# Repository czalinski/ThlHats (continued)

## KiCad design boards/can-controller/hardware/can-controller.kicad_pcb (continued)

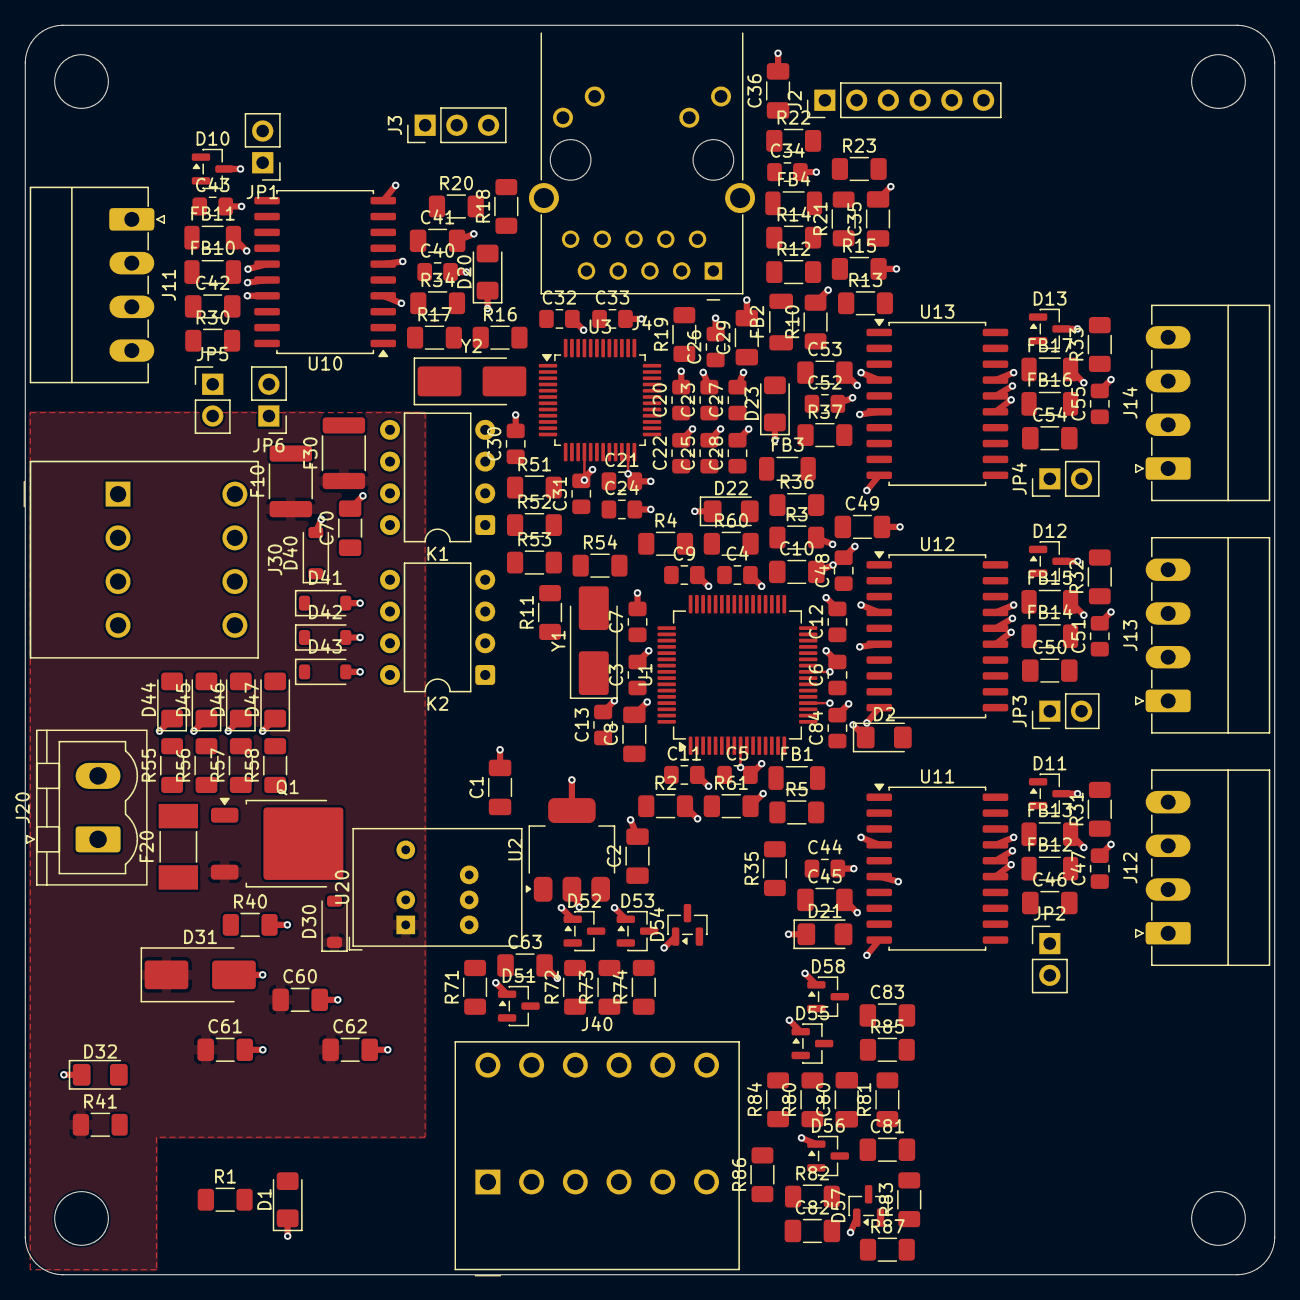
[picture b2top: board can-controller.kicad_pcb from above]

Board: 2 copper layers, 100.0 x 100.0 mm, 184 parts (0 on the bottom side), 129 nets.

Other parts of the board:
MH1, MH2, MH3, MH4: MountingHole_4.3mm_M4_Standoff7mm

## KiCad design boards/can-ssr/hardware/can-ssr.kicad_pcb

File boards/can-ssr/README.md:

# CAN SSR

Remote CAN FD node that turns a Mean Well adjustable supply into a simple
automatable DUT supply: high-side switch with reverse blocking, V and I
readback, remote voltage/current programming, auto-off when the host stops repeating its SET (failsafe timeout set by the host in each SET).
Requirements: [`docs/requirements.md`](../../docs/requirements.md), sections
4.2, 4.2.1 (builds and switching) and 4.2.2 (block diagram).

- Board: 100 x 100 mm, 2 layers, rev A (smaller welcome, not required)
- Mounting: stack interface (docs/requirements.md 4.4): 4 x M4 holes on a
  91 x 91 mm square, insulating (glass-filled nylon) 7 mm hex standoffs. Stacks
  up to 4 high on a can-controller, or screws to a DIN base plate on its own.
  No Pi holes, no DIN clips on the board (see board.json).
- Off the Pi header; powered from the 4-wire CAN cable (12 V)
- MCU: PIC18F47Q84-I/PT (TQFP-44), on the CAN/logic side

## Builds (one PCB, one firmware image)

| Build | MOSFETs (4 x D2PAK) | Max supply | Continuous |
|-------|---------------------|------------|------------|
| HC  | IPB021N10NM5LF2 | 60 V  | 50 A |
| STD | IPB107N20N3G   | 150 V | 25 A |
| HV  | IPB407N30N      | 200 V | 12 A (sequenced turn-on only) |

The only other difference is the **build resistor**, which sets the hardware
overcurrent trip threshold and is read by the PIC as the build ID.

## Functional blocks

| Block | Baseline parts | Domain |
|-------|----------------|--------|
| CAN, power, MCU | CAN FD transceiver, 12 V to 5 V buck, PIC18F47Q84-I/PT, address switch, termination jumper | CAN/logic |
| Display | MAX7219 (obsolete: replace in rev B, docs/rev-b-changes.md), 4-digit 7-segment LED, V/A indicators | CAN/logic |
| Overcurrent trip | Comparator + latch on the ACS770 output, threshold from the build resistor | CAN/logic |
| Barrier | 2 x VOM1271T, ACS770LCB-100U, ISO1640 I2C isolator, isolated DC-DC, photorelay | crosses |
| Power path | 4 x MOSFET (two per side, common source), gate network with slew C, freewheel diode, busbars, 4 bolts | load |
| Sense and programming | Vin/Vout dividers (~42 Hz RC), 2 x MCP3426 ADC (240 SPS each), 2 x MCP4725 DAC (Mean Well PV, PC), TLP240A remote on/off | load |

## Layout rules

- Busbar runs are mask-free top copper; four bolted ring-lug connections
  (supply +/-, load +/-).
- 250 V working clearances; about 6 mm creepage between the load side and the
  CAN/logic side. No copper pour joins the domains.

## Indicators and labels

- D4 (green) status, D5 (red) fault: there is no room for silkscreen labels;
  the colours identify them. D40 is the V indicator, D41 the A indicator
  (DIG4 segments A and B of the MAX7219).
- Mean Well connector J30: PV, PC, -V (supply -V / return bar), RC, RC
  (Remote ON/OFF photorelay contact, either polarity).
- One CAN pin legend above J1 covers J1 and J2 (same pinout).

## Fabrication

- PCBWay, 2 layers, 1.6 mm. **Production boards: 2 oz outer copper**
  (decided 2026-10-05; the extra board cost is less than the extra labour
  of adding more busbar). Prototypes may use 1 oz.
- Why: the VIN bar ends beside Q2. Q1's drain tab reaches it only through
  about 15-25 mm of board copper (about 19 mm wide). With 1 oz that path is about
  0.5 mOhm: about 0.3 W at 50 A (HC build), and Q2 carries about 55 % of the
  current. 2 oz halves both. The 12 A (HV) and 25 A (STD) builds hardly notice.

## Assembly

Rev A: leave the display unfitted (U40 MAX7219, U41, D40/D41, R50, C43/C44;
the MAX7219 is obsolete and expensive, rev B replaces it,
docs/rev-b-changes.md). The board works without it; readings go over CAN.

Busbars: C110 copper flat bar, 3.2 mm (1/8") thick. VIN, VOUT_SW and VOUT are
12.7 mm (1/2") wide; the source node is 6.35 mm (1/4"). Each solders onto a
strip of mask-free top copper:

| Bar | Width | Strip (board mm, x / y) | Next to |
|-----|-------|------------------------|---------|
| VIN | 1/2" | 111.65-124.35 / 186-199.2 | S+ bolt (H1, x 118); joins the VIN pour under Q1/Q2 |
| Source node | 1/4" | 130-136 / 159-184 | between the Q1/Q2 and Q3/Q4 source pins |
| VOUT_SW | 1/2" | 157-170 / 165-184 | right of the Q3/Q4 tabs; stops short of the ACS770 |
| VOUT | 1/2" | 175.65-188.35 / 171-199.2 | ACS770 output to the L+ bolt (H3, x 182) |
| Return | 1/2" | bottom side, 129.5-169.5 / 186.65-199.35, H2 (x 136) to H4 (x 163) | **not soldered**: clamped by the S- and L- bolts |

The bars sit beside the MOSFETs, not over them (D2PAK body 4.4 mm, bar
3.2 mm). The D2PAK drain tab is the solder joint and is almost entirely under
the package on solid copper, so it cannot be soldered with an iron alone. Build
the power section on a hot plate **before** any bottom-side parts are fitted.
The load side has many bottom parts (C10, C32, C33, C35, C37, C38, C40, C41,
D10-D13, Q5, R10-R15, R32-R47, U33, U34), and they would otherwise sit on the plate.

1. **Power section, bare board on a hot plate.** Paste the Q1-Q4 tab and pin
   pads. Place Q1-Q4, then reflow (preheat about 150 °C,
   then up to reflow). Either paste the bar strips and reflow the bars in the same
   pass, or tin the strips now and sweat the bars on afterwards with the board
   on the plate and a 100 W+ iron. Keep the bars square to their strips and
   clear of the ACS770 leads.
2. Let the board cool. Inspect the tab fillets at the exposed tab edge and touch up
   the gate/source pins with an iron.
3. **D13** (freewheel diode, SMC, bottom side): its anode pad is in the solid
   bottom return plane. Solder it first among the bottom parts, using hot air or
   a large tip with the board preheated.
4. **Bottom side** (iron): the other load-side parts listed above, then the trip
   cluster under the display (U20, Q20-Q24, R20-R29, C20-C23, D20).
5. **Top side** (iron): logic side and load-side sense parts. The ground pours connect
   pads solid (no thermal reliefs). Use a large tip, or preheat, on through-hole
   parts in the plane (U1, U2, U35, SW1, J1-J4, J30).
6. **ACS770 (U12)**: through-hole; solder last of the power parts with a large
   tip. Its leads sit on the VOUT_SW and VOUT copper.
7. **Bolts and lugs**: M5 through bar, board and ring lug, all lugs on top.
   S- and L- also clamp the bottom return bar. All four M4 holes take
   **insulating** standoffs only (MH3/MH4 sit in the load area).
8. Check that the MOSFETs fitted in step 1 and the build resistor match the
   intended build (Builds table), and tick the build on the silkscreen.

## Directories

- `hardware/` KiCad project
- `firmware/` firmware sources

## Stack interface rework (2026-10-06)

can-ssr stacks on a can-controller (up to 4 high) or lies side by side in a
1U/2U shelf; see docs/requirements.md 4.2 and 4.4. Done:

- MH1-MH4: `Thl_Mechanical:MountingHole_4.3mm_M4_Standoff7mm` at 4.5 mm from
  each corner. HOLE_KEEPOUT rule areas keep copper 4 mm from the load-side
  holes. A DRC rule lets MH2's standoff circle overlap U40's (empty) courtyard
  corner: U40's pin-24 lead is 4.45 mm from the hole centre, and the hex reaches 4.04 mm.
- Load bolts moved inward: S+ 18, S- 36, L- 63, L+ 82 mm (lug pitch 18 / 27 / 19
  mm, clear of the corner standoffs), with the bar strips, mask openings, the
  return bar (RETBAR), the VIN / RET top / VOUT pours, the S-/L- via rings and
  the labels. The BUILD tick boxes sit between S- and L-.
- Top-right corner: R6/D4 and R7/D5 down 2 mm, R50 and C44 left 0.85/0.8 mm;
  SEG_E, SEG_D, ISET, LED_STATUS, LED_FAULT, UART_RX, two +5V stubs and the
  C44 ground rerouted locally.

- CAN IN and CAN OUT share one double-level header, J1 = Phoenix MCDN 1,5/4-G1-3,5
  P26 THR (1953732), at the stack CAN position: left edge, pin 1 (CANH) at
  y 15.5 mm, pins down at 3.5 mm; pads n and n+4 are linked on the board (the
  +12 V link is 1 mm wide: it carries the supply for the boards further down the
  chain). Footprint `Thl_Connector:PhoenixContact_MCDN_1,5_4-G1-3,5_2x04_P3.5mm_Horizontal`
  from `lib/footprint_src/Thl_Connector/phoenix_mcdn.py`; its STEP is local-only
  (SamacSys licence). Which pin row feeds which plug level was not verified; it
  does not matter electrically, so the silkscreen just says CAN IN/OUT.
- Around it: SW1 right 3.0 mm, D2 into the old J2 space, the pin legend under
  J1; CANH, CANL, CAN_RX, V12_BUS, ADDR0-3, +5V and GND rejoined locally
  (tools/miniroute.py). The scripts that made these changes are in
  `hardware/stack_rework/` for reference (run once; do not rerun).

Still to do:

- Re-check the 12 V draw (estimate about 0.2 A at full display brightness):
  four boards share can-controller CAN1's PTC.

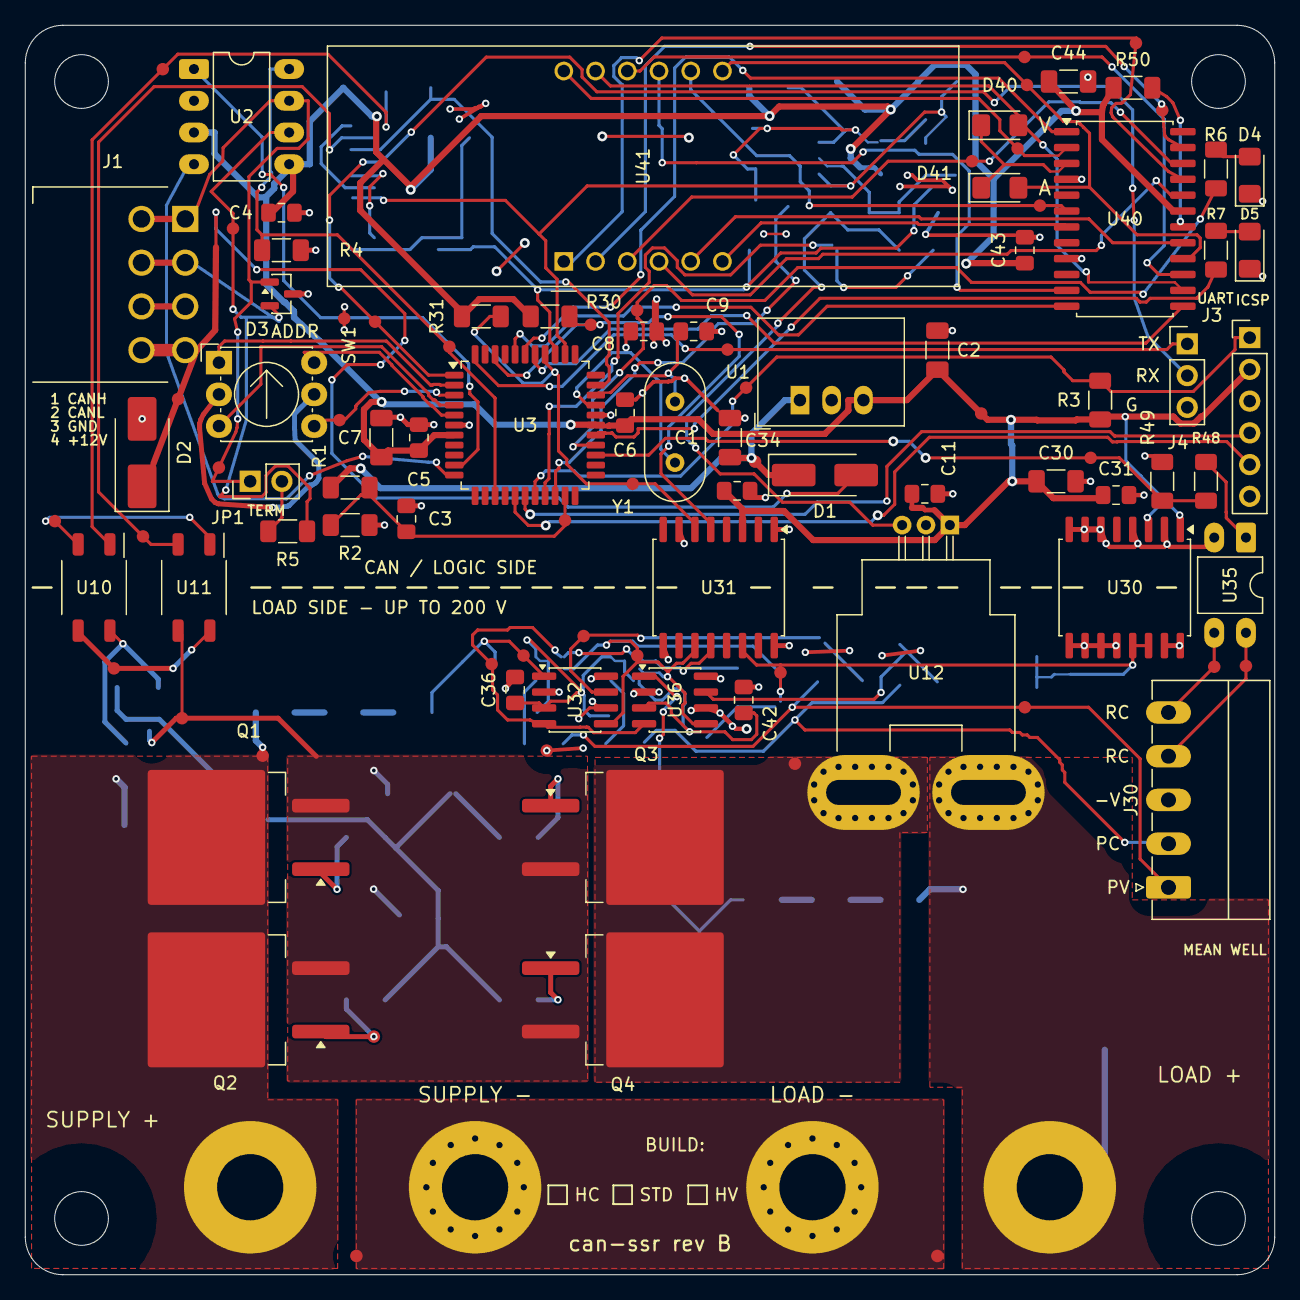
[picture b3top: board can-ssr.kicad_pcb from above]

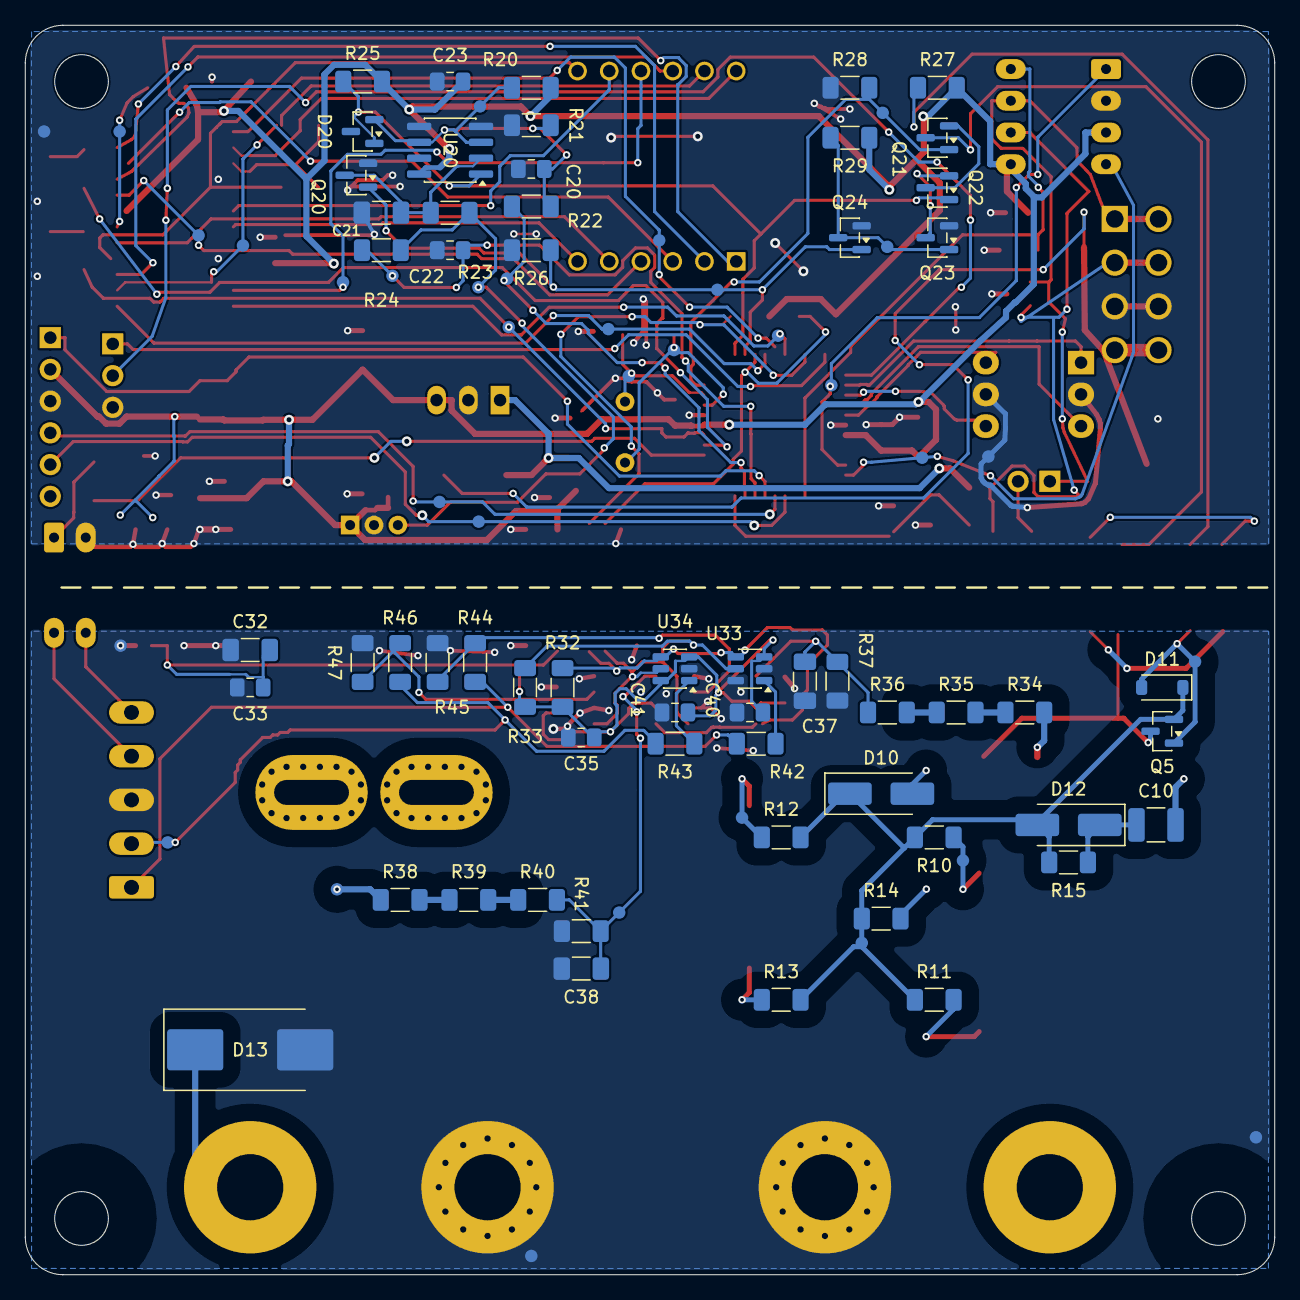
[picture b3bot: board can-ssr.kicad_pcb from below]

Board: 2 copper layers, 100.0 x 100.0 mm, 201 parts (91 on the bottom side), 91 nets.

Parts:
C1, C2, C7, C30, C32, C44: 10uF 25V X7R; C_1206_3216Metric_Pad1.33x1.80mm_HandSolder
C3, C4, C5, C6, C11, C20, C22, C23, C31, C33, C34, C35, C36, C40, C41, C42, C43: 100nF 50V X7R; C_0805_2012Metric_Pad1.18x1.45mm_HandSolder
C8, C9: 27pF 50V C0G; C_0805_2012Metric_Pad1.18x1.45mm_HandSolder
C10: 68nF 630V X7R; C_1210_3225Metric_Pad1.33x2.70mm_HandSolder
C21: 1nF 50V C0G; C_1206_3216Metric_Pad1.33x1.80mm_HandSolder
C37, C38: 470nF 50V X7R; C_1206_3216Metric_Pad1.33x1.80mm_HandSolder
D1: B340A; D_SMA_Handsoldering
D2: P6SMBJ15A; D_SMB_Handsoldering
D3: NUP2105L; SOT-23
D4, D40, D41: LED green; LED_1206_3216Metric_Pad1.42x1.75mm_HandSolder
D5: LED red; LED_1206_3216Metric_Pad1.42x1.75mm_HandSolder
D10: SMAZ15; D_SMA_Handsoldering
D11: 1N4148W; D_SOD-123
D12: ES1J; D_SMA_Handsoldering
D13: ES3J; D_SMC_Handsoldering
D20: BAT54; SOT-23
H1: SUPPLY +; MountingHole_5.3mm_M5_Pad
H2: SUPPLY -; MountingHole_5.3mm_M5_Pad
H3: LOAD +; MountingHole_5.3mm_M5_Pad
H4: LOAD -; MountingHole_5.3mm_M5_Pad
J1: CAN IN/OUT; PhoenixContact_MCDN_1,5_4-G1-3,5_2x04_P3.5mm_Horizontal
J3: ICSP; PinHeader_1x06_P2.54mm_Vertical
J4: UART; PinHeader_1x03_P2.54mm_Vertical
J30: MEAN WELL; PhoenixContact_MC_1,5_5-G-3.5_1x05_P3.50mm_Horizontal
JP1: TERM; PinHeader_1x02_P2.54mm_Vertical
MH1, MH2, MH3, MH4: MountingHole_4.3mm_M4_Standoff7mm
Q1, Q2, Q3, Q4: IPB107N20N3G; TO-263-2
Q5: MMBT2907A; SOT-23
Q20, Q21, Q22, Q23, Q24: 2N7002; SOT-23
R1: 47k; R_1206_3216Metric_Pad1.30x1.75mm_HandSolder
R2, R3, R4, R21, R25, R29, R45, R47: 10k; R_1206_3216Metric_Pad1.30x1.75mm_HandSolder
R5: 120R; R_1206_3216Metric_Pad1.30x1.75mm_HandSolder
R6, R7, R22, R23, R24, R42, R43: 1k; R_1206_3216Metric_Pad1.30x1.75mm_HandSolder
R10, R11, R12, R13: 10R; R_1206_3216Metric_Pad1.30x1.75mm_HandSolder
R14: 10M; R_1206_3216Metric_Pad1.30x1.75mm_HandSolder
R15: 1M; R_1206_3216Metric_Pad1.30x1.75mm_HandSolder
R20: 16.2k; R_1206_3216Metric_Pad1.30x1.75mm_HandSolder
R26, R28, R49: 100k; R_1206_3216Metric_Pad1.30x1.75mm_HandSolder
R27: 100R; R_1206_3216Metric_Pad1.30x1.75mm_HandSolder
R30, R31, R32, R33: 4.7k; R_1206_3216Metric_Pad1.30x1.75mm_HandSolder
R34, R35, R36, R38, R39, R40: 332k; R_1206_3216Metric_Pad1.30x1.75mm_HandSolder
R37, R41: 8.06k; R_1206_3216Metric_Pad1.30x1.75mm_HandSolder
R44, R46: 20k; R_1206_3216Metric_Pad1.30x1.75mm_HandSolder
R48: 680R; R_1206_3216Metric_Pad1.30x1.75mm_HandSolder
R50: 27k; R_1206_3216Metric_Pad1.30x1.75mm_HandSolder
SW1: ADDR; Nidec_Copal_SH-7010C
TP1, TP2, TP3, TP4, TP5, TP6, TP7, TP8, TP9, TP10, TP11, TP12, TP13, TP14, TP15, TP16, TP17, TP18, TP19, TP20, TP21, TP22, TP23, TP24, TP25, TP26, TP27, TP28, TP29, TP30, TP31, TP32, TP33, TP34, TP35, TP37, TP38, TP39, TP40, TP44, TP45, TP46, TP47, TP48, TP49, TP50, TP51, TP52, TP53, TP54, TP55, TP56, TP57, TP58, TP59, TP60, TP61, TP62, TP63, TP64, TP65, TP67, TP68, TP69, TP70, TP71, TP72, TP73: track; TP_Probe_D1.0mm
TP36, TP41, TP42, TP43, TP74, TP75: pour; TP_Probe_D1.0mm
TP66: via; TP_Probe_D1.0mm
U1: R-78E5.0-1.0; Converter_DCDC_RECOM_R-78E-0.5_THT
U2: MCP2562FD-E/P; DIP-8_W7.62mm_LongPads
U3: PIC18F47Q84-I/PT; TQFP-44_10x10mm_P0.8mm
U10, U11: VOM1271T; Vishay_SOP-4_4.4x4.9mm_P2.54mm_HandSolder
U12: ACS770LCB-100U-PFF-T; Allegro_CB_PFF
U20: LM393B; SOIC-8_3.9x4.9mm_P1.27mm
U30: UCC12050DVE; SOIC-16W_7.5x10.3mm_P1.27mm
U31: ISO1640DWR; SOIC-16W_7.5x10.3mm_P1.27mm
U32: MCP3426A0-E/SN; SOIC-8_3.9x4.9mm_P1.27mm
U33, U34: MCP4725A0T-E/CH; SOT-23-6
U35: TLP240A; DIP-4_W7.62mm_LongPads
U36: MCP3426A1-E/SN; SOIC-8_3.9x4.9mm_P1.27mm
U40: MAX7219CWG+; SOIC-24W_7.5x15.4mm_P1.27mm
U41: CC56-12SURKWA; CA56-12SRWA
Y1: 16MHz; Crystal_HC49-U_Vertical

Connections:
+5V: C2.1, C4.1, C5.1, C6.1, C7.1, C11.1, C23.1, C30.1, C31.1, C34.1, C43.1, C44.1, J3.2, R3.1, R20.1, R25.1, R27.1, R29.1, R30.1, R31.1, R50.1, TP24.1, U1.3, U2.3, U2.5, U3.7, U3.28, U12.1, U20.8, U30.1, U30.3, U31.3, U40.19
+12V: C1.1, D1.1, R1.1, TP23.1, U1.1
/CAN, power, MCU/ADDR0: SW1.1, U3.2
/CAN, power, MCU/ADDR1: SW1.2, TP20.1, U3.3
/CAN, power, MCU/ADDR2: SW1.4, U3.4
/CAN, power, MCU/ADDR3: SW1.8, U3.5
/CAN, power, MCU/CANH: D3.1, J1.1, J1.5, JP1.1, TP19.1, U2.7
/CAN, power, MCU/CANL: D3.2, J1.2, J1.6, R5.2, TP7.1, U2.6
/CAN, power, MCU/CAN_RX: TP64.1, U2.4, U3.11
/CAN, power, MCU/CAN_STBY: R4.1, TP13.1, U2.8, U3.14
/CAN, power, MCU/CAN_TX: TP61.1, U2.1, U3.10
/CAN, power, MCU/ICSPCLK: J3.5, TP63.1, U3.16
/CAN, power, MCU/ICSPDAT: J3.4, TP62.1, U3.17
/CAN, power, MCU/LED_FAULT: R7.1, TP55.1, U3.27
/CAN, power, MCU/LED_STATUS: R6.1, TP15.1, U3.26
/CAN, power, MCU/MCLR: J3.1, R3.2, TP17.1, U3.18
/CAN, power, MCU/OSC1: C8.1, TP58.1, U3.30, Y1.1
/CAN, power, MCU/OSC2: C9.1, TP57.1, U3.31, Y1.2
/CAN, power, MCU/TERM_A: JP1.2, R5.1
/CAN, power, MCU/UART_RX: J4.2, TP12.1, U3.1
/CAN, power, MCU/UART_TX: J4.1, TP16.1, U3.44
/CAN, power, MCU/V12_BUS: D1.2, D2.1, J1.4, J1.8, TP10.1
/CAN, power, MCU/V12_MON: C3.1, R1.2, R2.1, TP21.1, U3.21
/Display/DIG0: TP2.1, U40.2, U41.12
/Display/DIG1: TP51.1, U40.11, U41.9
/Display/DIG2: TP9.1, U40.6, U41.8
/Display/DIG3: U40.7, U41.6
/Display/DIG4: D40.1, D41.1, U40.3
/Display/ISET: R50.2, TP44.1, U40.18
/Display/SEG_A: D40.2, TP48.1, U40.14, U41.11
/Display/SEG_B: D41.2, TP4.1, U40.16, U41.7
/Display/SEG_C: TP47.1, U40.20, U41.4
/Display/SEG_D: TP6.1, U40.23, U41.2
/Display/SEG_DP: TP8.1, U40.22, U41.3
/Display/SEG_E: TP5.1, U40.21, U41.1
/Display/SEG_F: TP3.1, U40.15, U41.10
/Display/SEG_G: U40.17, U41.5
/Load-side sense and supply control/MW_PC: J30.2, R43.2, R46.1, TP68.1
/Load-side sense and supply control/MW_PV: J30.1, R42.2, R44.1, TP37.1
/Load-side sense and supply control/MW_RC_A: J30.4, TP39.1, U35.4
/Load-side sense and supply control/MW_RC_B: J30.5, TP38.1, U35.3
/Load-side sense and supply control/PC_DAC: R43.1, U34.1
/Load-side sense and supply control/PC_FB: R46.2, R47.1, U36.7
/Load-side sense and supply control/PV_DAC: R42.1, U33.1
/Load-side sense and supply control/PV_FB: R44.2, R45.1, TP27.1, U32.7
/Load-side sense and supply control/RLY_A: R48.2, U35.1
/Load-side sense and supply control/SCL_ISO: R33.2, TP34.1, U31.11, U32.5, U33.5, U34.5, U36.5
/Load-side sense and supply control/SDA_ISO: R32.2, TP31.1, U31.12, U32.4, U33.4, U34.4, U36.4
/Load-side sense and supply control/V5_ISO: C32.1, C33.1, C35.1, C36.1, C40.1, C41.1, C42.1, R32.1, R33.1, TP35.1, U30.13, U30.14, U31.14, U32.3, U33.3, U34.3, U34.6, U36.3
/Load-side sense and supply control/VIN_DIV: C37.1, R36.2, R37.1, TP32.1, U32.1
/Load-side sense and supply control/VOUT_DIV: C38.1, R40.2, R41.1, TP72.1, U36.1
/Overcurrent trip, gate drive/CMP_IN: C21.1, Q20.3, R23.2, U20.2
/Overcurrent trip, gate drive/EN_MID: Q21.2, Q22.3
/Overcurrent trip, gate drive/EN_MID2: Q22.2, Q23.3
/Overcurrent trip, gate drive/RST_INH: Q23.1, Q24.3, R29.2, TP50.1
/Overcurrent trip, gate drive/VTH: C20.1, D20.2, R20.2, R21.1, R22.1, TP45.1, U20.3, U20.6
/Power path/G1: Q1.1, R10.2, TP71.1
/Power path/G2: Q2.1, R11.2, TP40.1
/Power path/G3: Q3.1, R12.2, TP70.1
/Power path/G4: Q4.1, R13.2
/Power path/GATE: D10.1, D11.1, D12.2, Q5.2, R10.1, R11.1, R12.1, R13.1, R14.1, R15.2, TP73.1
/Power path/LED_MID: TP18.1, U10.2, U11.1
/Power path/SLEW: C10.2, D12.1, R15.1
/Power path/SRC: D10.2, Q1.3, Q2.3, Q3.3, Q4.3, Q5.3, R14.2, TP29.1, U11.3
/Power path/VOM_MID: TP28.1, U10.3, U11.4
/Power path/VOM_P: D11.2, Q5.1, TP67.1, U10.4
/Power path/VOUT_SW: Q3.2, Q4.2, TP36.1, U12.4
ACS_ADC: C22.1, R24.2, TP52.1, U3.19
ACS_OUT: R23.1, R24.1, TP53.1, U12.3
BUILD_REF: R22.2, TP54.1, U3.20
DISP_DIN: TP49.1, U3.39, U40.1
DISP_LOAD: TP60.1, U3.40, U40.12
DISP_SCK: TP56.1, U3.38, U40.13
GATE_EN: Q21.1, R28.1, TP46.1, U3.32
GND: C1.2, C2.2, C3.2, C4.2, C5.2, C6.2, C7.2, C8.2, C9.2, C11.2, C20.2, C21.2, C22.2, C23.2, C30.2, C31.2, C34.2, C43.2, C44.2, D2.2, D3.3, D4.1, D5.1, J1.3, J1.7, J3.3, J4.3, Q20.2, Q23.2, Q24.2, R2.2, R4.2, R21.2, R26.2, R28.2, R49.2, SW1.C, TP11.1, TP43.1, TP65.1, U1.2, U2.2, U3.6, U3.29, U12.2, U20.4, U20.5, U30.2, U30.4, U30.6, U30.7, U30.8, U31.1, U31.7, U35.2, U40.4, U40.9
GND_LOAD: C32.2, C33.2, C35.2, C36.2, C37.2, C38.2, C40.2, C41.2, C42.2, D13.2, H2.1, H4.1, J30.3, R37.2, R41.2, R45.2, R47.2, TP33.1, TP41.1, TP42.1, TP66.1, TP74.1, TP75.1, U30.9, U30.10, U30.11, U30.12, U30.15, U30.16, U31.9, U31.16, U32.2, U32.6, U32.8, U33.2, U33.6, U34.2, U36.2, U36.6, U36.8
I2C_SCL: R31.2, TP22.1, U3.37, U31.6
I2C_SDA: R30.2, TP14.1, U3.42, U31.5
MW_REMOTE: R48.1, R49.1, TP25.1, U3.25
unnamed: D4.2, R6.2
unnamed: D5.2, R7.2
unnamed: R34.2, R35.1
unnamed: R35.2, R36.1
unnamed: R38.2, R39.1
unnamed: R39.2, R40.1
TRIP_OK: D20.1, Q22.1, R25.2, U3.35, U20.1
TRIP_RST: Q20.1, Q24.1, R26.1, TP59.1, U3.36
VIN: C10.1, H1.1, Q1.2, Q2.2, R34.1, TP30.1
VOM_LED_A: R27.2, TP1.1, U10.1
VOM_LED_K: Q21.3, TP26.1, U11.2
VOUT: D13.1, H3.1, R38.1, TP69.1, U12.5

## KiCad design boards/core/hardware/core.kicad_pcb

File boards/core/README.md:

# Core: PIC32MK, 12 V power, Ethernet

Top board of the daughter-card stack (docs/requirements.md 4.0, 4.5).

- Board: 100 x 100 mm, 2 layers, rev A. 4 x M4 stack holes on a 91 x 91 mm
  square (`board.json` opts out of the Pi holes). No Pi header.
- U1 PIC32MK1024MCM064-I/PT, 12 MHz Abracon ABM3-12.000MHZ-B2-T, ICSP J2 and
  debug UART1 J5 (right-angle, top edge), heartbeat LED, VMID reference for
  the io-card.
- Power: J20 12 V in (side-entry MSTBA, right edge), F20, reverse-polarity
  Q1, TVS D31, TRACO TDN 5-2411WI (U20, the only RACK | LOGIC crossing),
  MCP1826S 3.3 V LDO.
- Ethernet: W6100 (U3) + Pulse JD0-0004NL RJ45 (bottom edge). 25 MHz crystal
  Y2 Abracon ABM3-25.000MHZ-D2Y-T (CL 18 pF, ±20 ppm, ESR 30 R) with 27 pF
  load caps C30/C31, the same as Y1's. A catalogue 5032 two-pad part with the
  W6100's typical 12 pF was not found. Gain margin is fine (gm 16.7 mA/V
  against about 1.9 mA/V critical). The estimated drive level is about
  80 uW against the ABM3's 100 uW max, so measure it on the first board.
  The fallback is NDK NX5032GA-25.000M LN-CD-1 (CL 8 pF, 500 uW, ±50 ppm)
  with about 8 pF caps.
- Stack: J10 2 x 20 logic bus and J11 2 x 3 rack power, **pin headers on the
  underside** (the core sits on top of the cards). Pinout and positions in
  `tools/stack_bus.py`; underside mounting swaps the pad columns
  (`stack_bus.underside`).

## Build files

- `hardware/gen_schematic.py`: schematic (bootstrap; stop using it once the
  schematic is edited in KiCad).
- `hardware/place.py`: outline, holes, placement, pours, +3V3 island under U1
  and 1V2D island under U3, RACK gap (rerunnable; leaves tracks alone).
- `hardware/route.py pre|auto|finish|all`: routing pipeline. **Do not rerun
  `pre` or `all` on the routed board**: they start over and erase hand routing.

## Status (2026-10-07)

Fully routed (last five connections by hand in KiCad), `tools/check_board.py`
clean: ERC, DRC and schematic parity without errors. Remaining warnings:

- no STEP models for U20 (TRACO TDN 5WI), F20 (NANO2) and J4 (Pulse
  JD0-0004NL: IGES only);
- silkscreen clipped by the board edge: J2/J5 (right-angle headers) and J20
  overhang the edge on purpose.

Clean-up after the hand routing: two +3V3 vias 0.48 mm apart merged, a
dangling +5V stub removed, a B.Cu GND sliver between J10 pins suppressed
(rule area GAP_SLIVER_J10 in place.py), mounting holes re-linked to
Thl_Mechanical, references tidied (`tools/silk_tidy.py`; 12 small parts keep
their reference on the Fab layer only, U1/U3/Y2 labelled on the body).

Parts chosen 2026-10-09: Y2 ABM3-25.000MHZ-D2Y-T, C30/C31 27 pF C0G
(KEMET C0805C270J5GACTU), C29 3.3 uF 25 V X7R 1206 (Samsung CL31B335KAHVPNE).

Open before ordering: mated stack height check against the cards.

Firmware: `firmware/` (bring-up console, can-card detection, CAN FD).

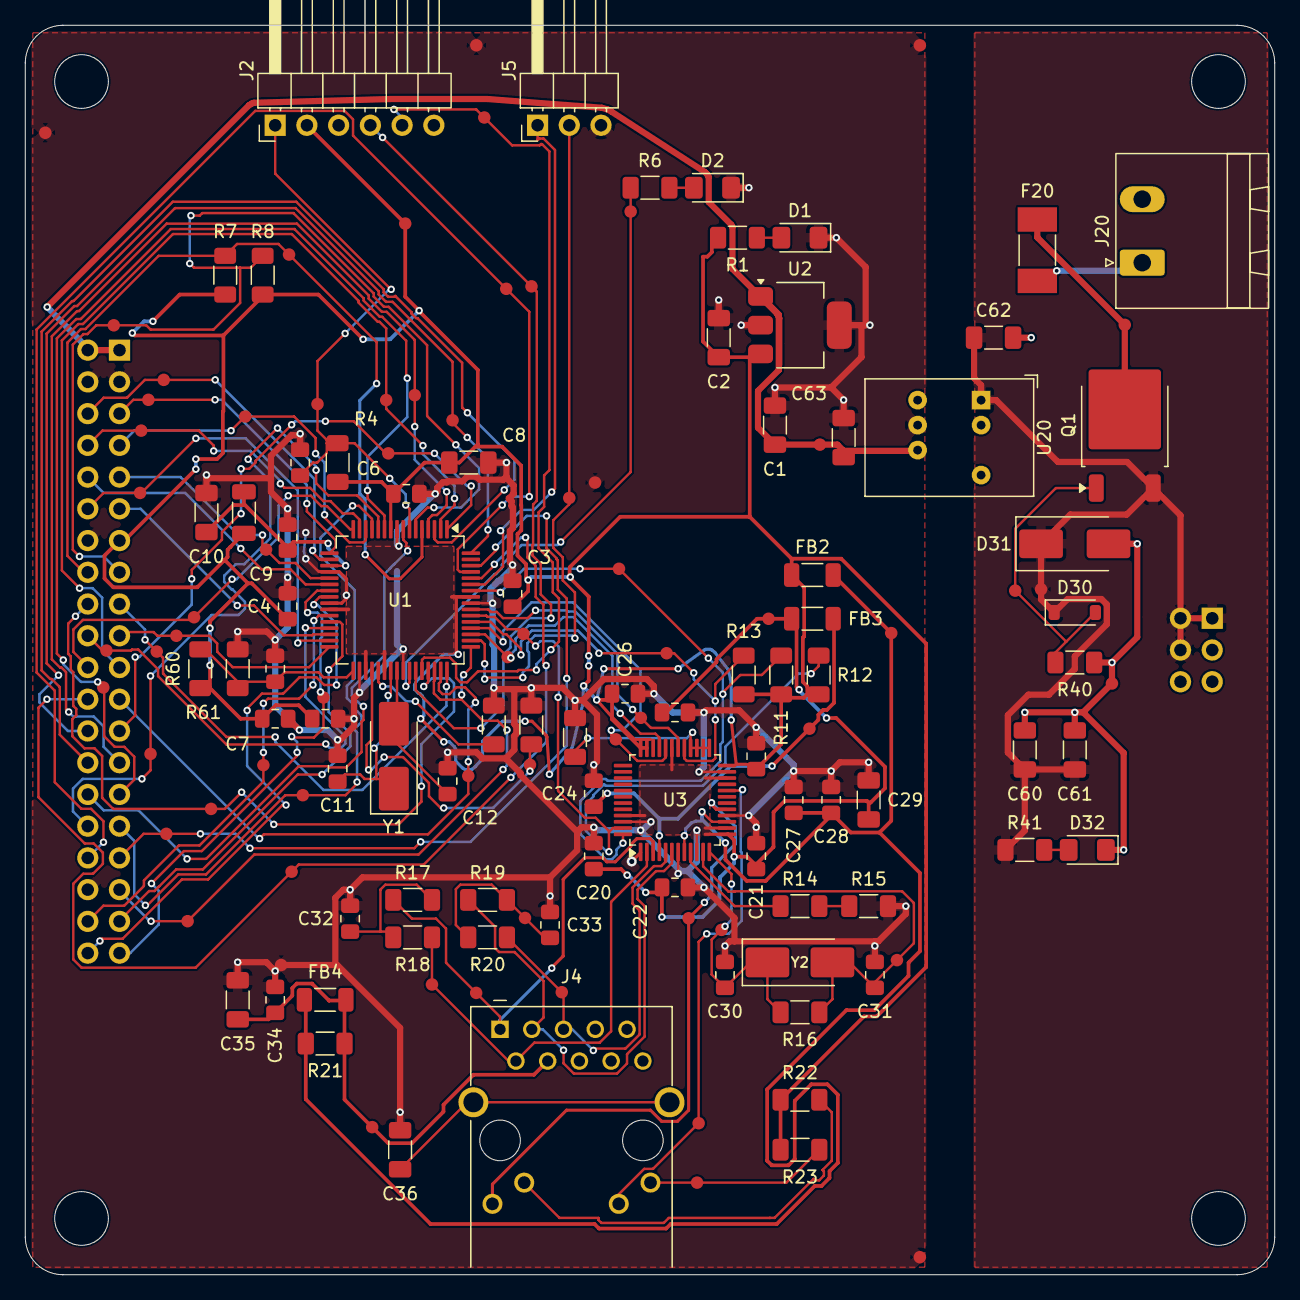
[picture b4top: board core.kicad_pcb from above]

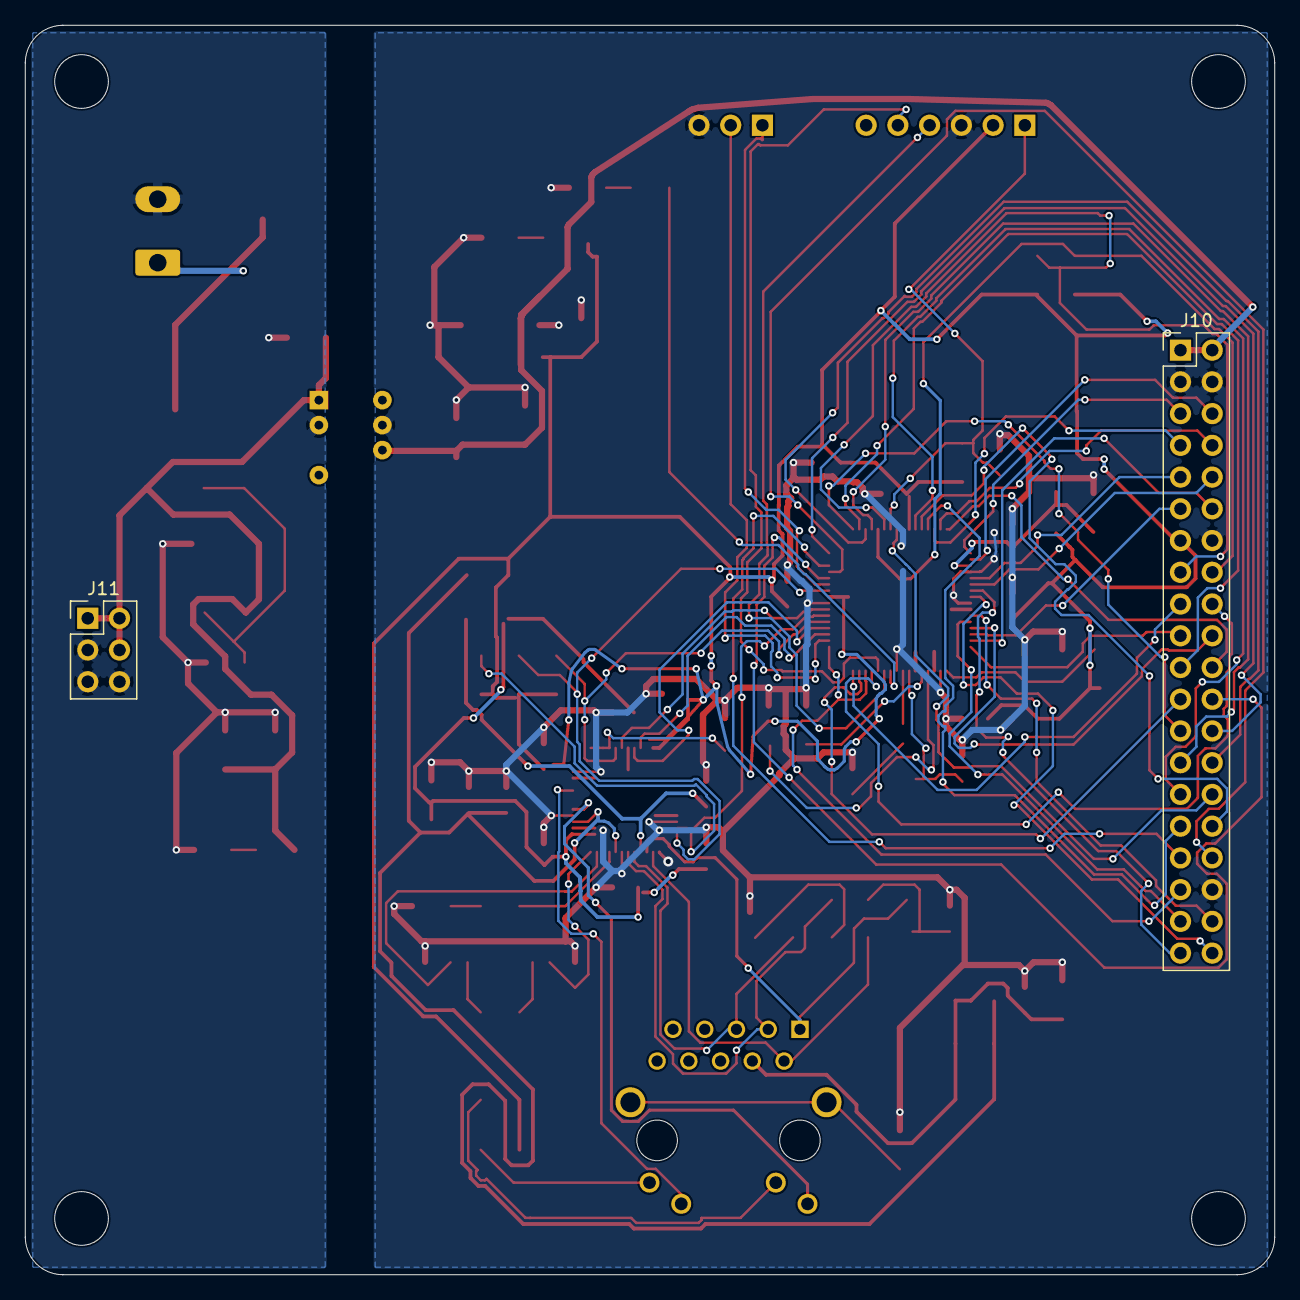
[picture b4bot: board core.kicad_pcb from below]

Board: 2 copper layers, 100.0 x 100.0 mm, 151 parts (2 on the bottom side), 82 nets.

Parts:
C1, C2, C8, C60, C61, C62, C63: 10uF 25V X7R; C_1206_3216Metric_Pad1.33x1.80mm_HandSolder
C3, C4, C5, C6, C7, C9, C13, C20, C21, C22, C23, C24, C25, C26, C27, C28, C32, C33, C34, C84: 100nF 50V X7R; C_0805_2012Metric_Pad1.18x1.45mm_HandSolder
C10, C35: 1uF 50V X7R; C_1206_3216Metric_Pad1.33x1.80mm_HandSolder
C11, C12, C30, C31: 27pF 50V C0G; C_0805_2012Metric_Pad1.18x1.45mm_HandSolder
C29: 3.3uF 25V X7R; C_1206_3216Metric_Pad1.33x1.80mm_HandSolder
C36: 1nF 2kV X7R; C_1206_3216Metric_Pad1.33x1.80mm_HandSolder
D1, D2, D32: LED green; LED_1206_3216Metric_Pad1.42x1.75mm_HandSolder
D30: 15V; D_SOD-123
D31: P6SMBJ15A; D_SMB_Handsoldering
F20: 4A; Fuse_Littelfuse-NANO2-451_453
FB1, FB2, FB3, FB4: HI1206P121R-10; L_1206_3216Metric_Pad1.22x1.90mm_HandSolder
J2: ICSP; PinHeader_1x06_P2.54mm_Horizontal
J4: JD0-0004NL; RJ45_Pulse_JD0-0004NL_Horizontal
J5: UART; PinHeader_1x03_P2.54mm_Horizontal
J10: STACK BUS; PinHeader_2x20_P2.54mm_Vertical
J11: RACK 12V; PinHeader_2x03_P2.54mm_Vertical
J20: 12V IN; PhoenixContact_MSTBA_2,5_2-G-5,08_1x02_P5.08mm_Horizontal
MH1, MH2, MH3, MH4: MountingHole_4.3mm_M4_Standoff7mm
Q1: SQD50P04-09L; TO-252-2
R1, R6: 1k; R_1206_3216Metric_Pad1.30x1.75mm_HandSolder
R2, R3, R4, R10, R11, R12, R13, R40, R60, R61: 10k; R_1206_3216Metric_Pad1.30x1.75mm_HandSolder
R7, R8, R41: 4.7k; R_1206_3216Metric_Pad1.30x1.75mm_HandSolder
R14: 12k; R_1206_3216Metric_Pad1.30x1.75mm_HandSolder
R15: 300R; R_1206_3216Metric_Pad1.30x1.75mm_HandSolder
R16: 1M; R_1206_3216Metric_Pad1.30x1.75mm_HandSolder
R17, R18, R19, R20: 49.9R; R_1206_3216Metric_Pad1.30x1.75mm_HandSolder
R21: 0R; R_1206_3216Metric_Pad1.30x1.75mm_HandSolder
R22, R23: 330R; R_1206_3216Metric_Pad1.30x1.75mm_HandSolder
TP1, TP2, TP4, TP23, TP64: pour; TP_Probe_D1.0mm
TP3, TP5, TP6, TP7, TP8, TP9, TP10, TP11, TP12, TP13, TP14, TP15, TP16, TP17, TP18, TP19, TP20, TP21, TP22, TP24, TP25, TP26, TP27, TP28, TP29, TP30, TP31, TP32, TP33, TP34, TP35, TP36, TP37, TP38, TP39, TP40, TP41, TP42, TP43, TP44, TP45, TP46, TP47, TP48, TP49, TP50, TP51, TP52, TP53, TP54, TP55, TP56, TP57, TP58, TP59, TP60, TP61, TP62, TP63: track; TP_Probe_D1.0mm
U1: PIC32MK1024MCM064-I/PT; TQFP-64_10x10mm_P0.5mm
U2: MCP1826S-3302E/DB; SOT-223-3_TabPin2
U3: W6100-L; LQFP-48_7x7mm_P0.5mm
U20: TDN 5-2411WI; Converter_DCDC_TRACO_TDN_5-xxxxWI_THT
Y1: 12MHz; Crystal_SMD_5032-2Pin_5.0x3.2mm_HandSoldering
Y2: 25MHz; Crystal_SMD_5032-2Pin_5.0x3.2mm_HandSoldering

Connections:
+3V3: C2.1, C3.1, C4.1, C5.1, C6.1, C7.1, C8.1, C25.1, C26.1, FB1.1, FB2.1, J2.2, J10.13, R1.1, R4.1, R7.1, R8.1, R11.1, R12.1, R13.1, R22.1, R23.1, R60.1, TP6.1, U1.10, U1.26, U1.35, U1.38, U1.57, U2.3, U3.24, U3.34, U3.35, U3.36
+5V: C1.1, C63.1, J10.1, J10.2, TP24.1, U2.1, U20.7
+12V: C60.1, C61.1, C62.1, D30.1, D31.1, J11.1, J11.2, J11.4, Q1.3, R41.1, TP33.1, U20.1
/12 V input, logic supply/D1_A: D1.2, R1.2
/12 V input, logic supply/D32_A: D32.2, R41.2
/12 V input, logic supply/Q1_G: D30.2, Q1.1, R40.1, TP32.1
/12 V input, logic supply/V12_F: F20.2, Q1.2, TP15.1
/12 V input, logic supply/V12_IN: F20.1, J20.1
/Ethernet/1V2A: C24.1, FB3.2, TP45.1, U3.4
/Ethernet/1V2D: C20.1, C21.1, C22.1, C23.1, C29.1, FB3.1, TP30.1, U3.13, U3.14, U3.22, U3.31, U3.45
/Ethernet/3V3A: C27.1, C28.1, FB2.2, FB4.1, R21.1, TP31.1, U3.8, U3.15
/Ethernet/ACTn: J4.13, TP62.1, U3.20
/Ethernet/CHASSIS: C36.1, J4.SH
/Ethernet/JCT: C34.1, C35.1, FB4.2, J4.4, R21.2, TP61.1
/Ethernet/LEDG_A: J4.12, R22.2
/Ethernet/LEDY_A: J4.14, R23.2, TP63.1
/Ethernet/LNKn: J4.11, TP58.1, U3.17
/Ethernet/MOD: R10.1, U3.25, U3.26, U3.27, U3.28
/Ethernet/RSET: R14.1, U3.9
/Ethernet/RSET2: R14.2, R15.1
/Ethernet/RXCT: C33.1, R19.2, R20.1, TP56.1
/Ethernet/RXN: J4.5, R20.2, TP57.1, U3.5
/Ethernet/RXP: J4.3, R19.1, U3.6
/Ethernet/TXCT: C32.1, R17.2, R18.1
/Ethernet/TXN: J4.2, R18.2, TP54.1, U3.2
/Ethernet/TXP: J4.1, R17.1, TP55.1, U3.3
/Ethernet/XSCI: C30.1, R16.1, TP59.1, U3.12, Y2.1
/Ethernet/XSCO: C31.1, R16.2, TP60.1, U3.11, Y2.2
/MCU/AVDD: C9.1, C10.1, FB1.2, U1.19
/MCU/D2_A: D2.2, R6.2
/MCU/LED_HB: R6.1, TP7.1, U1.42
/MCU/MCLR: C13.1, J2.1, R4.2, TP19.1, U1.7
/MCU/OSC1: C11.1, U1.39, Y1.1
/MCU/OSC2: C12.1, U1.40, Y1.2
/MCU/PGC2: J2.5, TP3.1, U1.44
/MCU/PGD2: J2.4, TP14.1, U1.43
/MCU/U1RX: J5.2, TP22.1, U1.50
/MCU/U1TX: J5.1, U1.59
/MCU/USB_DN: R3.1, TP41.1, U1.36
/MCU/USB_DP: R2.1, U1.37
/MCU/VMID_REF: C84.1, R60.2, R61.1, U1.33
AI1N: J10.37, U1.28
AI1P: J10.38, TP38.1, U1.27
AI2N: J10.39, TP39.1, U1.23
AI2P: J10.40, U1.24
C1RX: J10.5, TP9.1, U1.17
C1TX: J10.6, TP10.1, U1.18
C2RX: J10.7, TP18.1, U1.14
C2TX: J10.8, TP17.1, U1.15
C3RX: J10.9, TP27.1, U1.21
C3TX: J10.10, U1.22
C4RX: J10.11, U1.30
C4TX: J10.12, TP16.1, U1.31
DE1: J10.26, TP21.1, U1.64
DE2: J10.25, TP20.1, U1.1
ETH_CS: R13.2, TP44.1, U1.53, U3.29
ETH_INT: R12.2, TP28.1, U1.54, U3.47
ETH_MISO: TP40.1, U1.51, U3.33
ETH_MOSI: TP42.1, U1.52, U3.32
ETH_RST: R11.2, TP29.1, U1.58, U3.48
ETH_SCK: TP43.1, U1.55, U3.30
GND: C1.2, C2.2, C3.2, C4.2, C5.2, C6.2, C7.2, C8.2, C9.2, C10.2, C11.2, C12.2, C13.2, C20.2, C21.2, C22.2, C23.2, C24.2, C25.2, C26.2, C27.2, C28.2, C29.2, C30.2, C31.2, C32.2, C33.2, C34.2, C35.2, C36.2, C63.2, C84.2, D1.1, D2.1, J2.3, J5.3, J10.3, J10.4, J10.14, J10.36, R2.2, R3.2, R10.2, R15.2, R61.2, TP1.1, TP2.1, TP4.1, TP23.1, TP53.1, TP64.1, U1.9, U1.20, U1.25, U1.34, U1.41, U1.56, U2.2, U3.1, U3.7, U3.10, U3.16, U3.23, U3.46, U20.6
GND_RACK: C60.2, C61.2, C62.2, D31.2, D32.1, J11.3, J11.5, J11.6, J20.2, R40.2, TP46.1, U20.2
GPIO1: J10.32, TP36.1, U1.12
GPIO2: J10.31, TP50.1, U1.13
GPIO3: J10.34, TP13.1, U1.61
GPIO4: J10.33, TP47.1, U1.62
RLY1: J10.28, U1.3
RLY2: J10.27, TP12.1, U1.4
RLY3: J10.30, U1.8
RLY4: J10.29, TP34.1, U1.11
SCL: J10.16, R7.2, TP5.1, U1.5
SDA: J10.15, R8.2, TP8.1, U1.6
U2RX: J10.17, TP37.1, U1.48
U2TX: J10.18, TP48.1, U1.45
U3RX: J10.19, TP25.1, U1.32
U3TX: J10.20, TP35.1, U1.29
U4RX: J10.21, TP11.1, U1.2
U4TX: J10.22, TP26.1, U1.16
U5RX: J10.23, TP51.1, U1.47
U5TX: J10.24, TP49.1, U1.60
VMID: J10.35, TP52.1, U1.46, U1.49
